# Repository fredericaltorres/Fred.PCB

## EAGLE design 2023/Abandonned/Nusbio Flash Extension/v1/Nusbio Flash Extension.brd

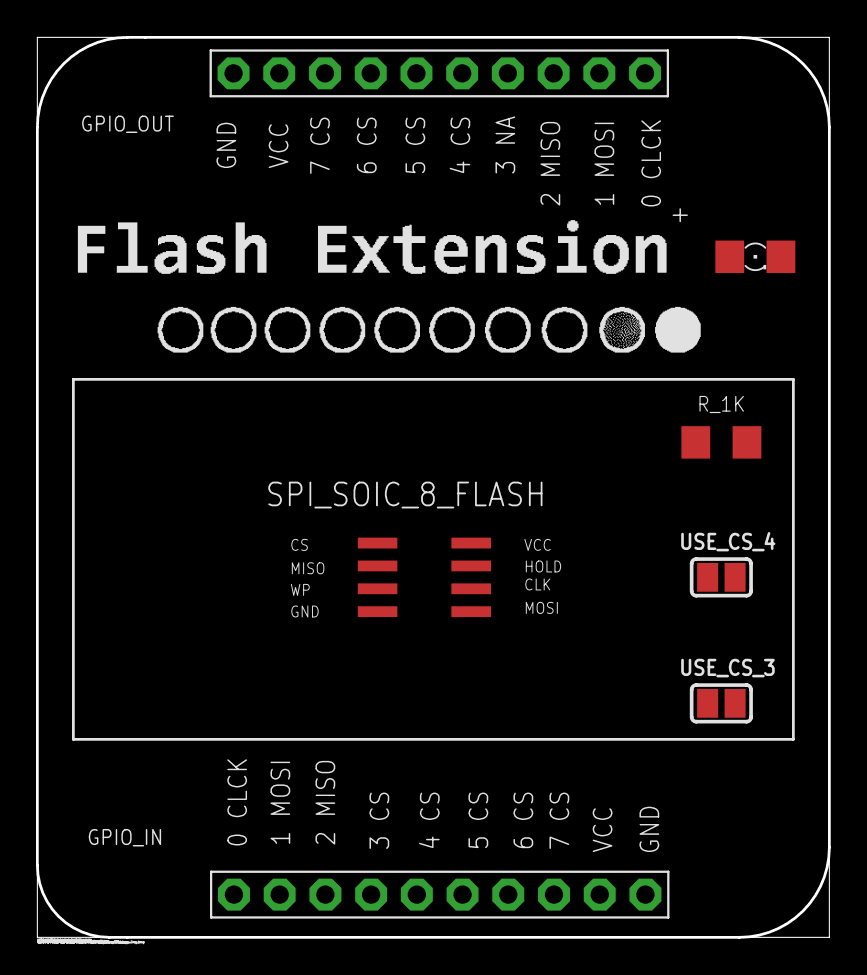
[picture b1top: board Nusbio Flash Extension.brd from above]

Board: 2 copper layers, 44.0 x 50.0 mm, 7 parts (0 on the bottom side), 12 nets, no tracks yet.

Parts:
GPIO_IN: PINHD-1X10; 1X10-BIG
GPIO_OUT: PINHD-1X10; 1X10-BIG
LED_POWER: 1206
R_1K: R1206
SPI_SOIC_8_FLASH: 25AA080SN; SO-08
USE_CS_3, USE_CS_4: SOLDERJUMPER_REFLOW

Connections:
CS: SPI_SOIC_8_FLASH.1, USE_CS_3.2, USE_CS_4.2
CS_4: GPIO_IN.4, GPIO_OUT.4, USE_CS_3.1
CS_5: GPIO_IN.5, GPIO_OUT.5, USE_CS_4.1
GND: GPIO_IN.10, GPIO_OUT.10, R_1K.1, SPI_SOIC_8_FLASH.4
GPIO6: GPIO_IN.6, GPIO_OUT.6
GPIO7: GPIO_IN.7, GPIO_OUT.7
GPIO8: GPIO_IN.8, GPIO_OUT.8
MISO: GPIO_IN.3, GPIO_OUT.3, SPI_SOIC_8_FLASH.2
MOSI: GPIO_IN.2, GPIO_OUT.2, SPI_SOIC_8_FLASH.5
unnamed: LED_POWER.C, R_1K.2
SCK: GPIO_IN.1, GPIO_OUT.1, SPI_SOIC_8_FLASH.6
VCC: GPIO_IN.9, GPIO_OUT.9, LED_POWER.A, SPI_SOIC_8_FLASH.3, SPI_SOIC_8_FLASH.7, SPI_SOIC_8_FLASH.8

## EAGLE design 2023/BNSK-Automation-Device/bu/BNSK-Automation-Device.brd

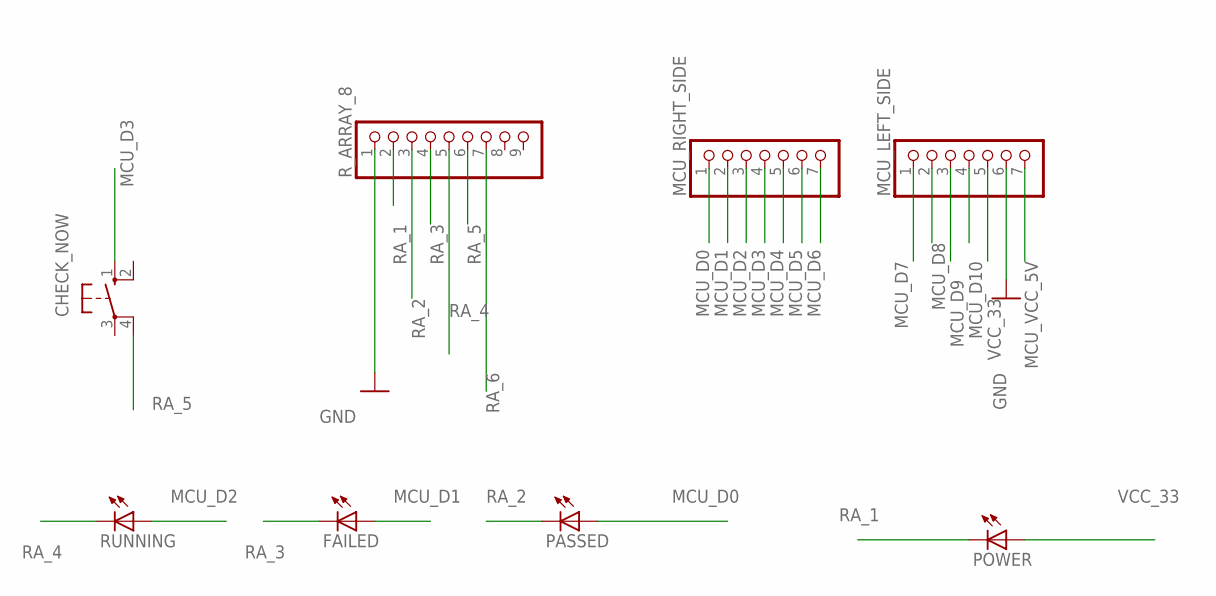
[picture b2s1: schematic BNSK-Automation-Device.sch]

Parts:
CHECK_NOW: 10-XX; B3F-10XX
FAILED: LEDSMT1206; 1206
MCU_LEFT_SIDE: PINHD-1X7; 1X07
MCU_RIGHT_SIDE: PINHD-1X7; 1X07
PASSED: LEDSMT1206; 1206
POWER: LEDSMT1206; 1206
RUNNING: LEDSMT1206; 1206
R_ARRAY_8: PINHD-1X9; 1X09-BIG

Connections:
GND: MCU_LEFT_SIDE.6, R_ARRAY_8.1
MCU_D0: MCU_RIGHT_SIDE.1, PASSED.A
MCU_D1: FAILED.A, MCU_RIGHT_SIDE.2
MCU_D2: MCU_RIGHT_SIDE.3, RUNNING.A
MCU_D3: CHECK_NOW.1 (S), MCU_RIGHT_SIDE.4
MCU_D4: MCU_RIGHT_SIDE.5
MCU_D5: MCU_RIGHT_SIDE.6
MCU_D6: MCU_RIGHT_SIDE.7
MCU_D7: MCU_LEFT_SIDE.1
MCU_D8: MCU_LEFT_SIDE.2
MCU_D9: MCU_LEFT_SIDE.3
MCU_D10: MCU_LEFT_SIDE.4
MCU_VCC_5V: MCU_LEFT_SIDE.7
RA_1: POWER.C, R_ARRAY_8.2
RA_2: PASSED.C, R_ARRAY_8.3
RA_3: FAILED.C, R_ARRAY_8.4
RA_4: RUNNING.C, R_ARRAY_8.5
RA_5: CHECK_NOW.4 (P1), R_ARRAY_8.6
RA_6: R_ARRAY_8.7
VCC_33: MCU_LEFT_SIDE.5, POWER.A

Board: 2 copper layers, 8 parts (0 on the bottom side), 11 nets, no tracks yet.

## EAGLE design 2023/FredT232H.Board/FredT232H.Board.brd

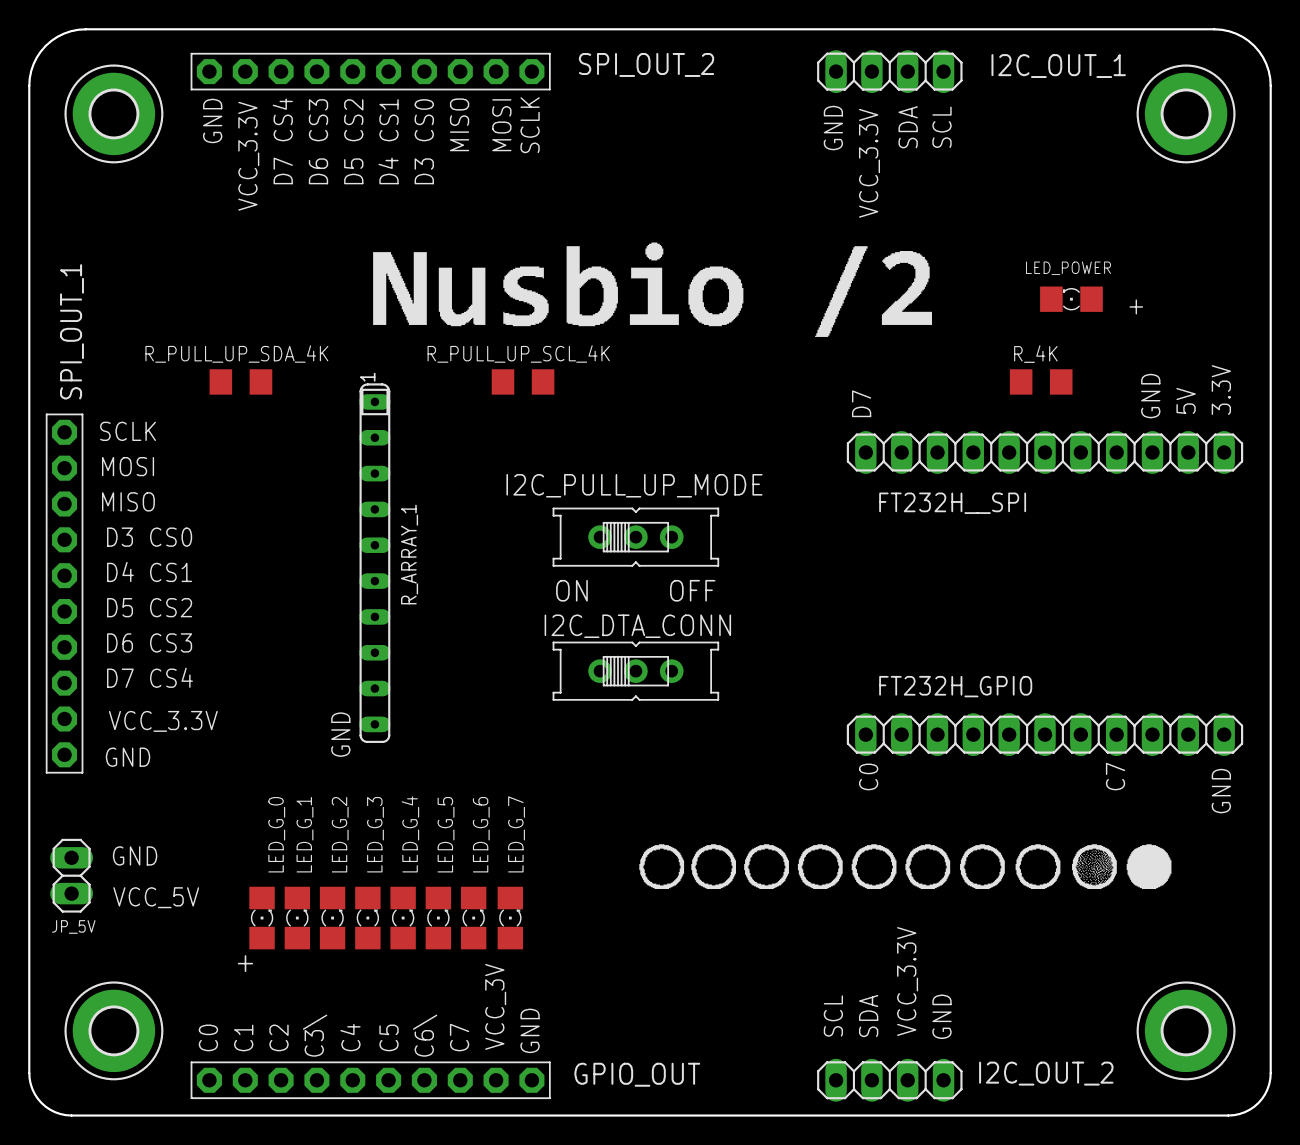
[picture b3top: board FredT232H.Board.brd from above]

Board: 2 copper layers, 88.0 x 77.0 mm, 27 parts (0 on the bottom side), 29 nets, no tracks yet.

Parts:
FT232H_GPIO, FT232H__SPI: 1X11
GPIO_OUT: PINHD-1X10; 1X10-BIG
H1, H2, H3, H4: MOUNT-PAD-ROUND3.3; 3,3-PAD
I2C_DTA_CONN, I2C_PULL_UP_MODE: EG1218
I2C_OUT_1, I2C_OUT_2: 1X04
JP_5V: 1X02
LED_G_0, LED_G_1, LED_G_2, LED_G_3, LED_G_4, LED_G_5, LED_G_6, LED_G_7: 1206
LED_POWER: 1206
R_4K: R1206
R_ARRAY_1: SIP10
R_PULL_UP_SCL_4K: R1206
R_PULL_UP_SDA_4K: R1206
SPI_OUT_1, SPI_OUT_2: PINHD-1X10; 1X10-BIG

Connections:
C0: FT232H_GPIO.1, GPIO_OUT.10, LED_G_0.A
C1: FT232H_GPIO.2, GPIO_OUT.9, LED_G_1.A
C2: FT232H_GPIO.3, GPIO_OUT.8, LED_G_2.A
C3: FT232H_GPIO.4, GPIO_OUT.7, LED_G_3.A
C4: FT232H_GPIO.5, GPIO_OUT.6, LED_G_4.A
C5: FT232H_GPIO.6, GPIO_OUT.5, LED_G_5.A
C6: FT232H_GPIO.7, GPIO_OUT.4, LED_G_6.A
C7: FT232H_GPIO.8, GPIO_OUT.3, LED_G_7.A
D0_SCLK: FT232H__SPI.8, I2C_OUT_1.1, I2C_OUT_2.1, R_PULL_UP_SCL_4K.1, SPI_OUT_1.10, SPI_OUT_2.10
D1_MOSI: FT232H__SPI.7, I2C_DTA_CONN.P, R_PULL_UP_SDA_4K.1, SPI_OUT_1.9, SPI_OUT_2.9
D2_MISO: FT232H__SPI.6, I2C_DTA_CONN.O, I2C_OUT_1.2, I2C_OUT_2.2, SPI_OUT_1.8, SPI_OUT_2.8
D3_CS0: FT232H__SPI.5, SPI_OUT_1.7, SPI_OUT_2.7
D4_CS1: FT232H__SPI.4, SPI_OUT_1.6, SPI_OUT_2.6
D5_CS2: FT232H__SPI.3, SPI_OUT_1.5, SPI_OUT_2.5
D6_CS3: FT232H__SPI.2, SPI_OUT_1.4, SPI_OUT_2.4
D7_CS4: FT232H__SPI.1, SPI_OUT_1.3, SPI_OUT_2.3
GND: FT232H_GPIO.11, FT232H__SPI.9, GPIO_OUT.1, H1.B3,3, H2.B3,3, H3.B3,3, H4.B3,3, I2C_OUT_1.4, I2C_OUT_2.4, JP_5V.1, R_4K.1, R_ARRAY_1.1, SPI_OUT_1.1, SPI_OUT_2.1
unnamed: LED_POWER.C, R_4K.2
unnamed: I2C_PULL_UP_MODE.O, R_PULL_UP_SCL_4K.2, R_PULL_UP_SDA_4K.2
R_G_0: LED_G_0.C, R_ARRAY_1.2
R_G_1: LED_G_1.C, R_ARRAY_1.3
R_G_2: LED_G_2.C, R_ARRAY_1.4
R_G_3: LED_G_3.C, R_ARRAY_1.5
R_G_4: LED_G_4.C, R_ARRAY_1.6
R_G_5: LED_G_5.C, R_ARRAY_1.7
R_G_6: LED_G_6.C, R_ARRAY_1.8
R_G_7: LED_G_7.C, R_ARRAY_1.9
VCC_5: FT232H__SPI.10, JP_5V.2, LED_POWER.A
VCC_33: FT232H__SPI.11, GPIO_OUT.2, I2C_OUT_1.3, I2C_OUT_2.3, I2C_PULL_UP_MODE.P, SPI_OUT_1.2, SPI_OUT_2.2

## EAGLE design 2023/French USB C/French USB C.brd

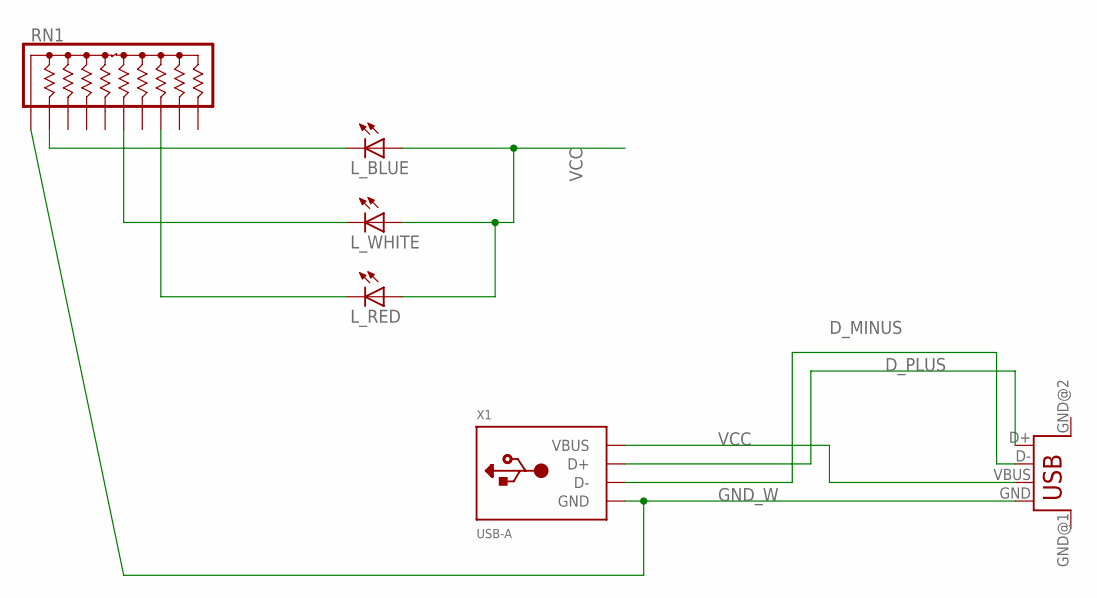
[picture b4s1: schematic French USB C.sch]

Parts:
L_BLUE: LED5MM
L_RED: LED5MM
L_WHITE: LED5MM
RN1: 4610X; SIP10
U$1: USB; USB-FEMALE-A-PTH
X1: USB-A; MOLEX_480371000

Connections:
D_MINUS: U$1.D-, X1.2 (D-)
D_PLUS: U$1.D+, X1.3 (D+)
GND_W: RN1.1, U$1.GND, X1.4 (GND)
unnamed: L_BLUE.K (C), RN1.2
unnamed: L_RED.K (C), RN1.8
unnamed: L_WHITE.K (C), RN1.6
VCC: L_BLUE.A, L_RED.A, L_WHITE.A, U$1.VBUS, X1.1 (VBUS)

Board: 2 copper layers, 6 parts (0 on the bottom side), 7 nets, no tracks yet.

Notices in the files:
parts and their libraries:
microbuilder: This work is placed in the public domain, and may be freely used for commercial and non-commercial work with the following conditions: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
